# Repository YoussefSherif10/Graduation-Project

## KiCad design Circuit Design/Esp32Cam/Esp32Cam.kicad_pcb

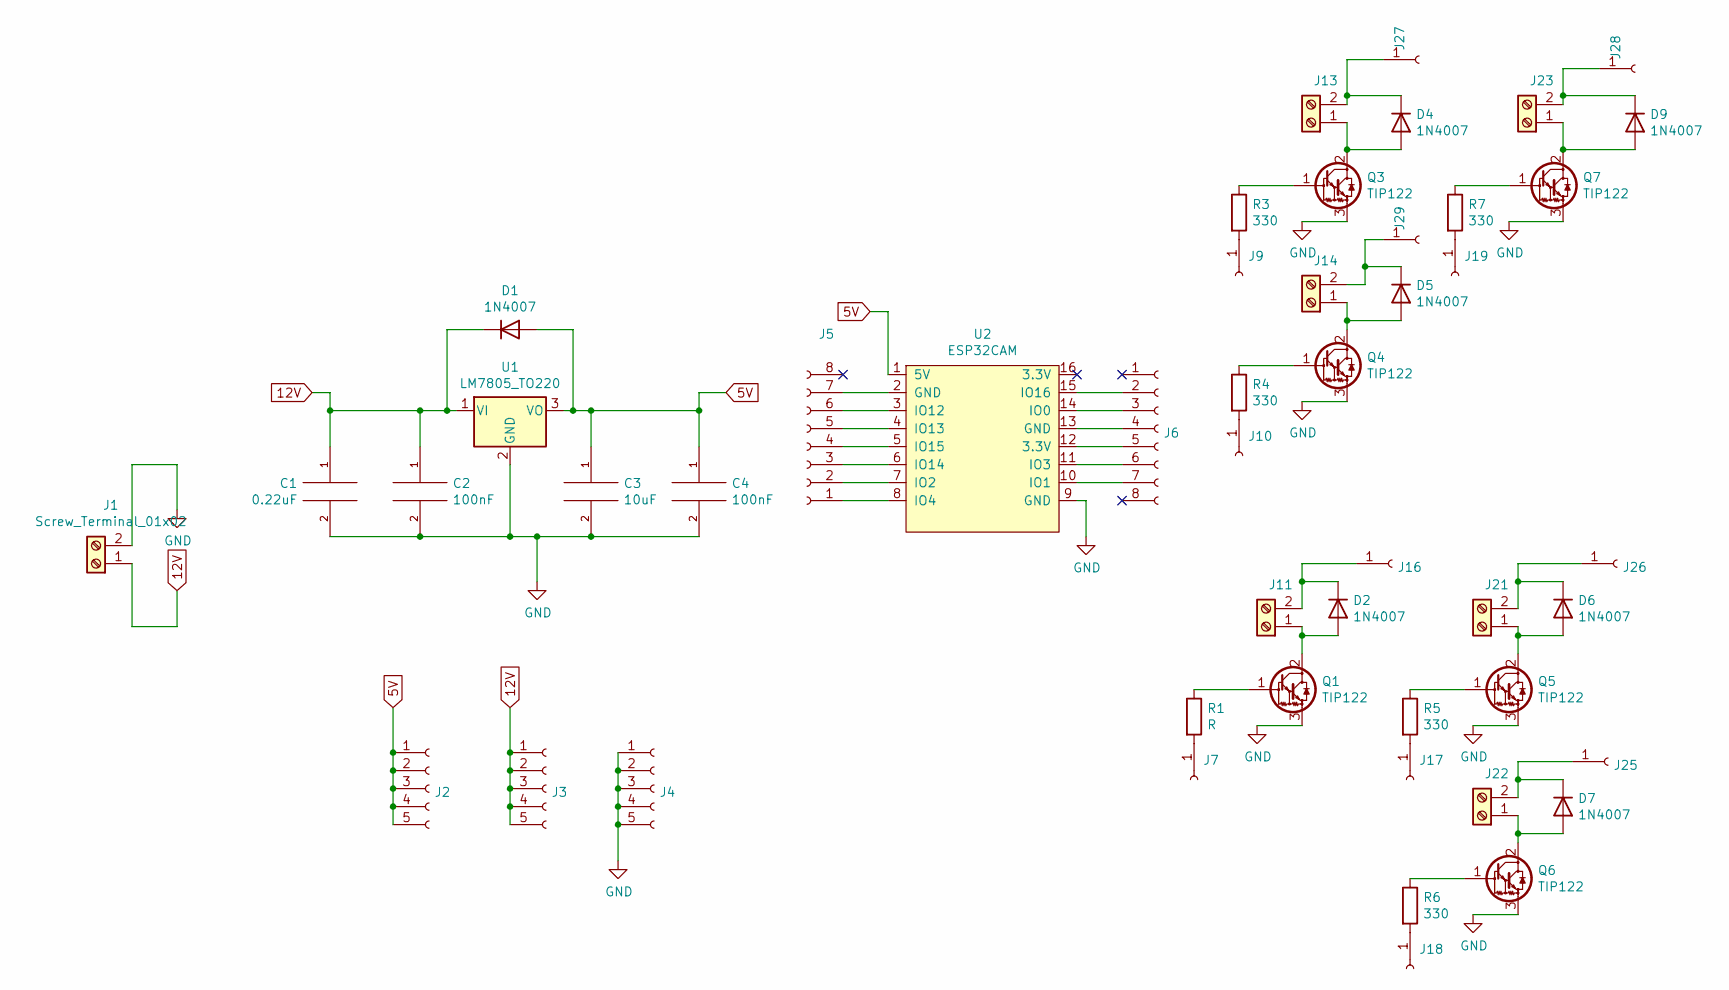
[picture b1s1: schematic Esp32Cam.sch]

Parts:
C1: 0.22uF; C_Disc_D5.0mm_W2.5mm_P2.50mm
C2, C4: 100nF; C_Disc_D5.0mm_W2.5mm_P2.50mm
C3: 10uF; CP_Radial_D8.0mm_P2.50mm
D1, D2, D4, D5, D6, D7, D9: 1N4007; D_DO-41_SOD81_P10.16mm_Horizontal
J1, J11, J13, J14, J21, J22, J23: Screw_Terminal_01x02; TerminalBlock_bornier-2_P5.08mm
J2, J3, J4: Conn_01x05_Female; PinHeader_1x05_P2.54mm_Vertical
J5, J6: Conn_01x08_Female; PinHeader_1x08_P2.54mm_Vertical
J7, J9, J10, J16, J17, J18, J19, J25, J26, J27, J28, J29: Conn_01x01_Female; PinHeader_1x01_P2.54mm_Vertical
Q1, Q3, Q4, Q5, Q6, Q7: TIP122; TO-220-3_Vertical
R1: R; R_Axial_DIN0207_L6.3mm_D2.5mm_P10.16mm_Horizontal
R3, R4, R5, R6, R7: 330; R_Axial_DIN0207_L6.3mm_D2.5mm_P10.16mm_Horizontal
U1: LM7805_TO220; TO-220-3_Vertical
U2: ESP32CAM

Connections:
5V: C3.1, C4.1, D1.2 (A), J2.1, J2.2, J2.3, J2.4, J2.5, U1.3 (VO), U2.1 (5V)
12V: C1.1, C2.1, D1.1 (K), J1.1, J3.1, J3.2, J3.3, J3.4, J3.5, U1.1 (VI)
GND: C1.2, C2.2, C3.2, C4.2, J1.2, J4.1, J4.2, J4.3, J4.4, J4.5, Q1.3 (E), Q3.3 (E), Q4.3 (E), Q5.3 (E), Q6.3 (E), Q7.3 (E), U1.2 (GND), U2.9 (GND)
unnamed: D2.1 (K), J11.2, J16.1
unnamed: D2.2 (A), J11.1, Q1.2 (C)
unnamed: D4.1 (K), J13.2, J27.1
unnamed: D4.2 (A), J13.1, Q3.2 (C)
unnamed: D5.1 (K), J14.2, J29.1
unnamed: D5.2 (A), J14.1, Q4.2 (C)
unnamed: D6.1 (K), J21.2, J26.1
unnamed: D6.2 (A), J21.1, Q5.2 (C)
unnamed: D7.1 (K), J22.2, J25.1
unnamed: D7.2 (A), J22.1, Q6.2 (C)
unnamed: D9.1 (K), J23.2, J28.1
unnamed: D9.2 (A), J23.1, Q7.2 (C)
unnamed: J5.1, U2.8 (IO4)
unnamed: J5.2, U2.7 (IO2)
unnamed: J5.3, U2.6 (IO14)
unnamed: J5.4, U2.5 (IO15)
unnamed: J5.5, U2.4 (IO13)
unnamed: J5.6, U2.3 (IO12)
unnamed: J5.7, U2.2 (GND)
unnamed: J6.2, U2.15 (IO16)
unnamed: J6.3, U2.14 (IO0)
unnamed: J6.4, U2.13 (GND)
unnamed: J6.5, U2.12 (3.3V)
unnamed: J6.6, U2.11 (IO3)
unnamed: J6.7, U2.10 (IO1)
unnamed: J7.1, R1.2
unnamed: J9.1, R3.2
unnamed: J10.1, R4.2
unnamed: J17.1, R5.2
unnamed: J18.1, R6.2
unnamed: J19.1, R7.2
unnamed: Q1.1 (B), R1.1
unnamed: Q3.1 (B), R3.1
unnamed: Q4.1 (B), R4.1
unnamed: Q5.1 (B), R5.1
unnamed: Q6.1 (B), R6.1
unnamed: Q7.1 (B), R7.1

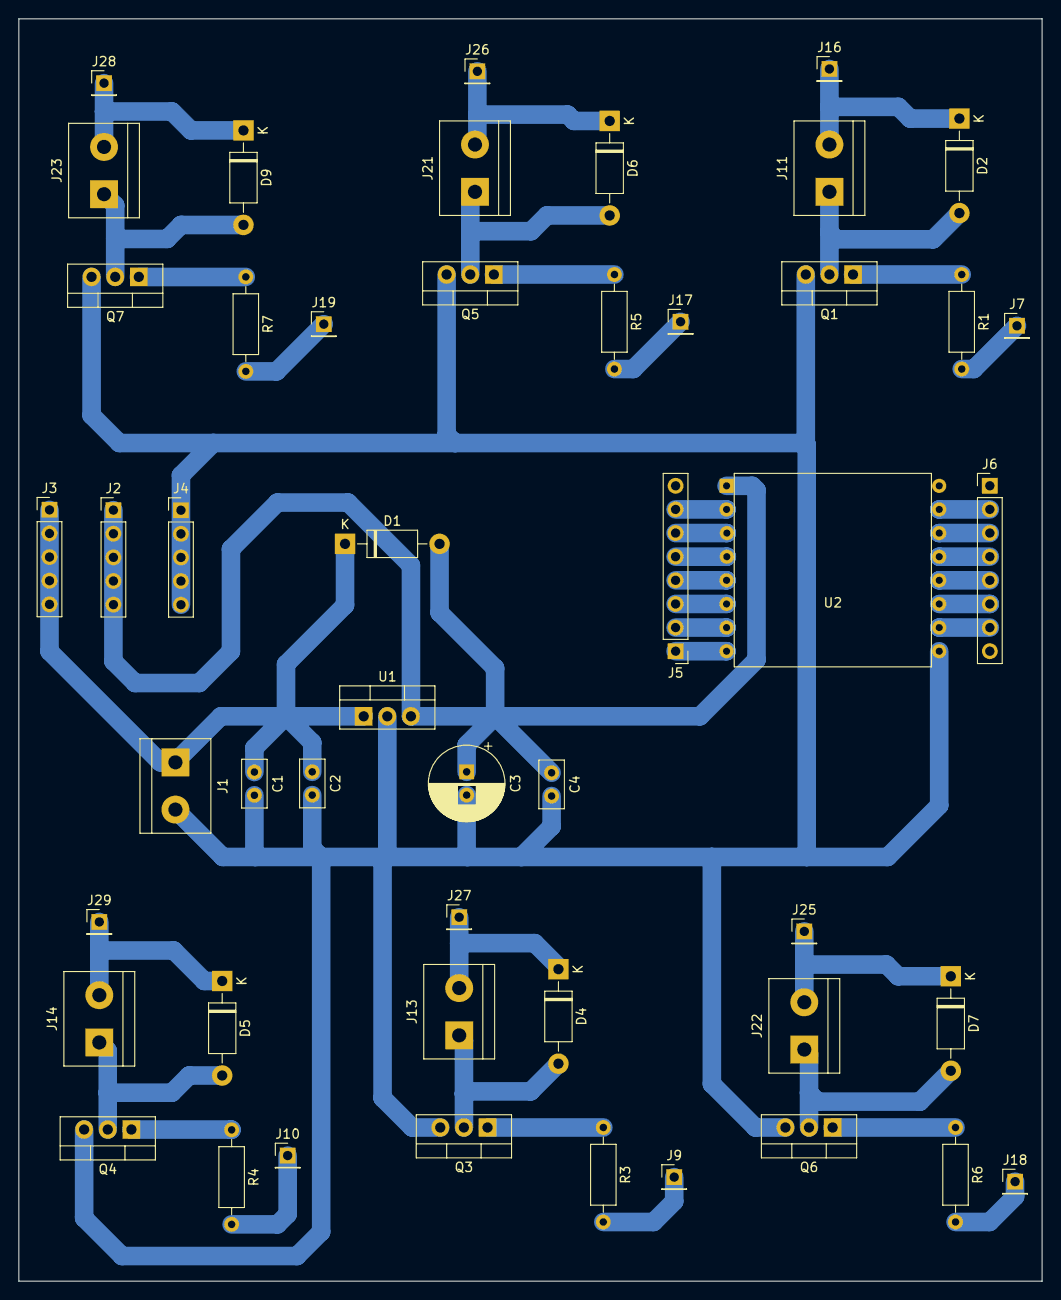
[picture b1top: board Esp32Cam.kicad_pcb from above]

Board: 2 copper layers, 110.0 x 135.7 mm, 49 parts (0 on the bottom side), 40 nets.

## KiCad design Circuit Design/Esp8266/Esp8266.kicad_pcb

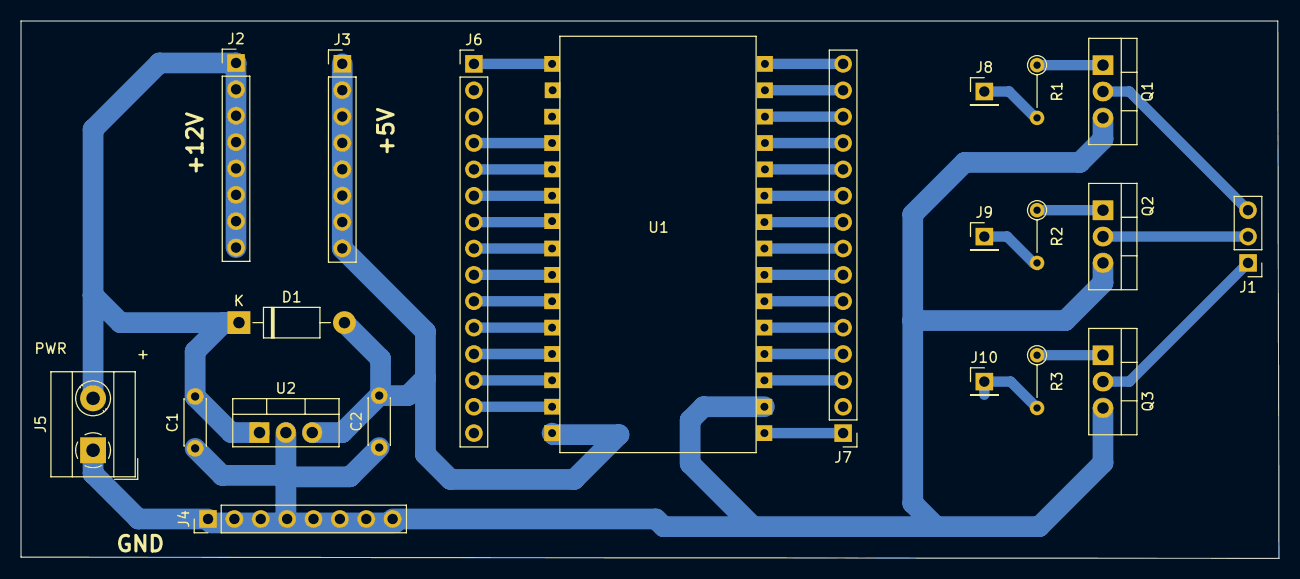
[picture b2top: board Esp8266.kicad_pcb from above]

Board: 2 copper layers, 121.2 x 51.8 mm, 21 parts (0 on the bottom side), 38 nets.

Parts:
C1: 330nF; C_Disc_D4.3mm_W1.9mm_P5.00mm
C2: 100nF; C_Disc_D4.3mm_W1.9mm_P5.00mm
D1: 1N4007; D_DO-41_SOD81_P10.16mm_Horizontal
J1: Conn_01x03_Male; PinHeader_1x03_P2.54mm_Vertical
J2: 12V; PinHeader_1x08_P2.54mm_Vertical
J3: 5V; PinHeader_1x08_P2.54mm_Vertical
J4: GND; PinHeader_1x08_P2.54mm_Vertical
J5: ScrewTerminal; TerminalBlock_MetzConnect_Type055_RT01502HDWU_1x02_P5.00mm_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
J6, J7: Conn_01x15_Male; PinHeader_1x15_P2.54mm_Vertical
J8, J9, J10: Conn_01x01_Male; PinHeader_1x01_P2.54mm_Vertical
Q1, Q2, Q3: TIP122; TO-220-3_Vertical
R1, R2, R3: 1K; R_Axial_DIN0204_L3.6mm_D1.6mm_P5.08mm_Vertical
U1: Node8266; NodeMcu
U2: L7805; TO-220-3_Vertical

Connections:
5V: C2.2, D1.2, J3.1, J3.2, J3.3, J3.4, J3.5, J3.6, J3.7, J3.8, U1.30, U2.3
+12V: C1.2, D1.1, J2.1, J2.2, J2.3, J2.4, J2.5, J2.6, J2.7, J2.8, J5.2, U2.1
GND: C1.1, C2.1, J4.1, J4.2, J4.3, J4.4, J4.5, J4.6, J4.7, J4.8, J5.1, Q1.3, Q2.3, Q3.3, U1.14, U2.2
unnamed: J1.1, Q3.2
unnamed: J1.2, Q2.2
unnamed: J1.3, Q1.2
unnamed: J6.1, U1.16
unnamed: J6.4, U1.19
unnamed: J6.5, U1.20
unnamed: J6.6, U1.21
unnamed: J6.7, U1.22
unnamed: J6.8, U1.23
unnamed: J6.9, U1.24
unnamed: J6.10, U1.25
unnamed: J6.11, U1.26
unnamed: J6.12, U1.27
unnamed: J6.13, U1.28
unnamed: J6.14, U1.29
unnamed: J7.1, U1.15
unnamed: J7.3, U1.13
unnamed: J7.4, U1.12
unnamed: J7.5, U1.11
unnamed: J7.6, U1.10
unnamed: J7.7, U1.9
unnamed: J7.8, U1.8
unnamed: J7.9, U1.7
unnamed: J7.10, U1.6
unnamed: J7.11, U1.5
unnamed: J7.12, U1.4
unnamed: J7.13, U1.3
unnamed: J7.14, U1.2
unnamed: J7.15, U1.1
unnamed: J8.1, R1.2
unnamed: J9.1, R2.2
unnamed: J10.1, R3.2
unnamed: Q1.1, R1.1
unnamed: Q2.1, R2.1
unnamed: Q3.1, R3.1
